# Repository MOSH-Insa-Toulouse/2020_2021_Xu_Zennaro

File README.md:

# 2020_2021_Xu_Zennaro

MOSH-KiCAD Project

# TASKS

- [x] MOSH
- [x] KiCAD

---

### KiCad - Shield for Arduino

- [x] Créer un projet de PCB pour réaliser une shield Arduino
- [x] Saisi du schéma
- [x] Vérification des tests électriques **ERC**
- [x] Association des empreintes de composants avec leur boitier
- [ ] Combiner les modèles 3D aux empreintes
- [x] Génération de la netlist
- [x] Placement des composants
- [x] Router les pistes de la carte électronique

#### KiCad Tools used

[KiCad EDA - Schematic Capture & PCB Design Software](https://kicad-pcb.org/), version: 5.1.8

Open source EDA / electronics CAD software for Windows, macOS and Linux.

#### Librairies de composants

* LTC1050:
* Resistor_THT:R_Axial_DIN0207_L6.3mm_D2.5mm_P10.16mm_Horizontal
* Capacitor
* Arduino Uno
* Conn_01x03:Pin
* RN2483

## Electrical diagram

## Component placement

## Routage

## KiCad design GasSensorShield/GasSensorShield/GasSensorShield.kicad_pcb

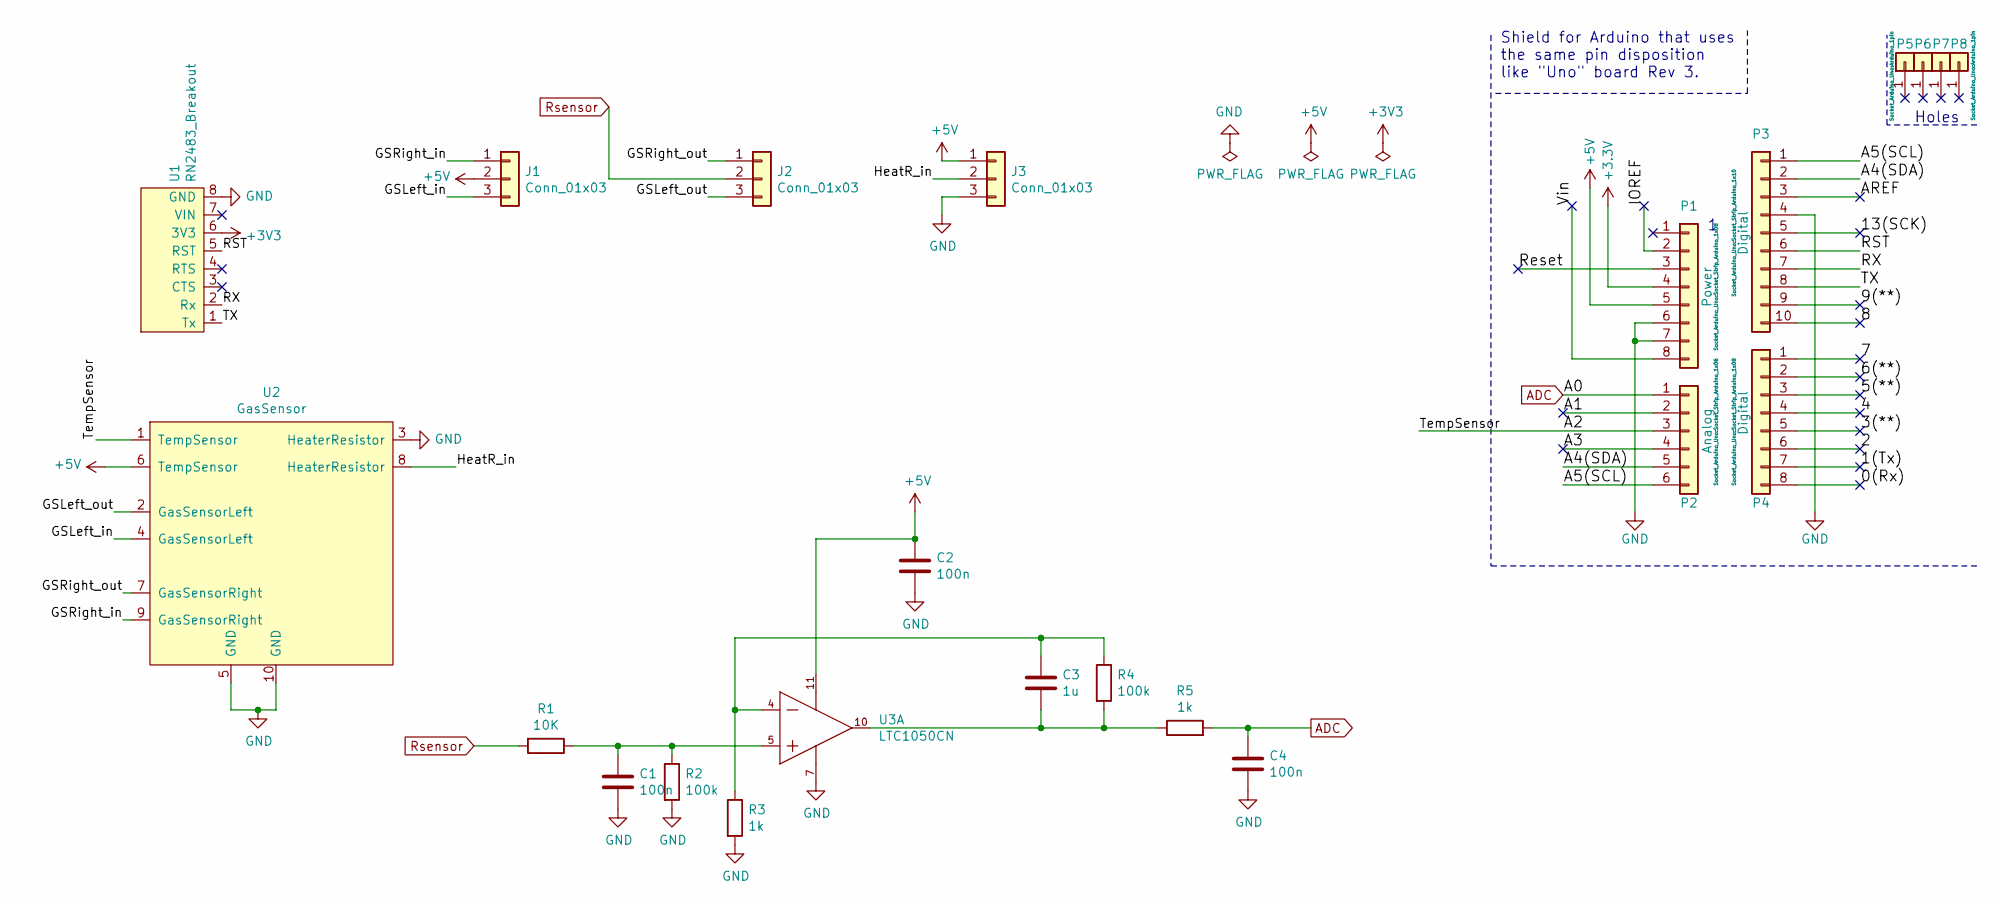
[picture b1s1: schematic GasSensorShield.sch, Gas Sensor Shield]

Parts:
C1, C2, C4: 100n; C_Disc_D4.3mm_W1.9mm_P5.00mm
C3: 1u; C_Disc_D4.3mm_W1.9mm_P5.00mm
J1, J2, J3: Conn_01x03; PinHeader_1x03_P2.00mm_Vertical
P1: Power; Socket_Strip_Arduino_1x08
P2: Analog; Socket_Strip_Arduino_1x06
P3: Digital; Socket_Strip_Arduino_1x10
P4: Digital; Socket_Strip_Arduino_1x08
P5, P6, P7, P8: CONN_01X01; Arduino_1pin
R1: 10K; R_Axial_DIN0207_L6.3mm_D2.5mm_P10.16mm_Horizontal
R2, R4: 100k; R_Axial_DIN0207_L6.3mm_D2.5mm_P10.16mm_Horizontal
R3, R5: 1k; R_Axial_DIN0207_L6.3mm_D2.5mm_P10.16mm_Horizontal
U1: RN2483_Breakout; Module_RN2483_Breakout
U2: GasSensor; TO-5-10
U3: LTC1050CN; Linear_Technology-LTC1050CN-Manufacturer_Recommended

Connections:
+5V: C2.1, J1.2, J3.1, P1.5, U2.6 (TempSensor), U3.11 (V+)
/0(Rx): P4.8
/1(Tx): P4.7
/2: P4.6
/3(**): P4.5
/4: P4.4
/5(**): P4.3
/6(**): P4.2
/7: P4.1
/8: P3.10
/9(**): P3.9
/13(SCK): P3.5
/A1: P2.2
/A2: P2.3, U2.1 (TempSensor)
/A3: P2.4
/A4(SDA): P2.5, P3.2
/A5(SCL): P2.6, P3.1
/AREF: P3.3
/GSLeft_in: J1.3, U2.4 (GasSensorLeft)
/GSLeft_out: J2.3, U2.2 (GasSensorLeft)
/GSRight_in: J1.1, U2.9 (GasSensorRight)
/GSRight_out: J2.1, U2.7 (GasSensorRight)
/HeatR_in: J3.2, U2.8 (HeaterResistor)
/IOREF: P1.2
/RST: P3.6, U1.5 (RST)
/RX: P3.7, U1.2 (Rx)
/Reset: P1.3
/TX: P3.8, U1.1 (Tx)
/Vin: P1.8
ADC: C4.1, P2.1, R5.2
GND: C1.2, C2.2, C4.2, J3.3, P1.6, P1.7, P3.4, R2.2, R3.2, U1.8 (GND), U2.3 (HeaterResistor), U2.5 (GND), U2.10 (GND), U3.7 (V-)
unnamed: C1.1, R1.1, R2.1, U3.5 (+IN)
unnamed: C3.1, R3.1, R4.1, U3.4 (-IN)
unnamed: C3.2, R4.2, R5.1, U3.10 (OUT)
Rsensor: J2.2, R1.2

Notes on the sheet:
Holes
Shield for Arduino that uses the same pin disposition like "Uno" board Rev 3.

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
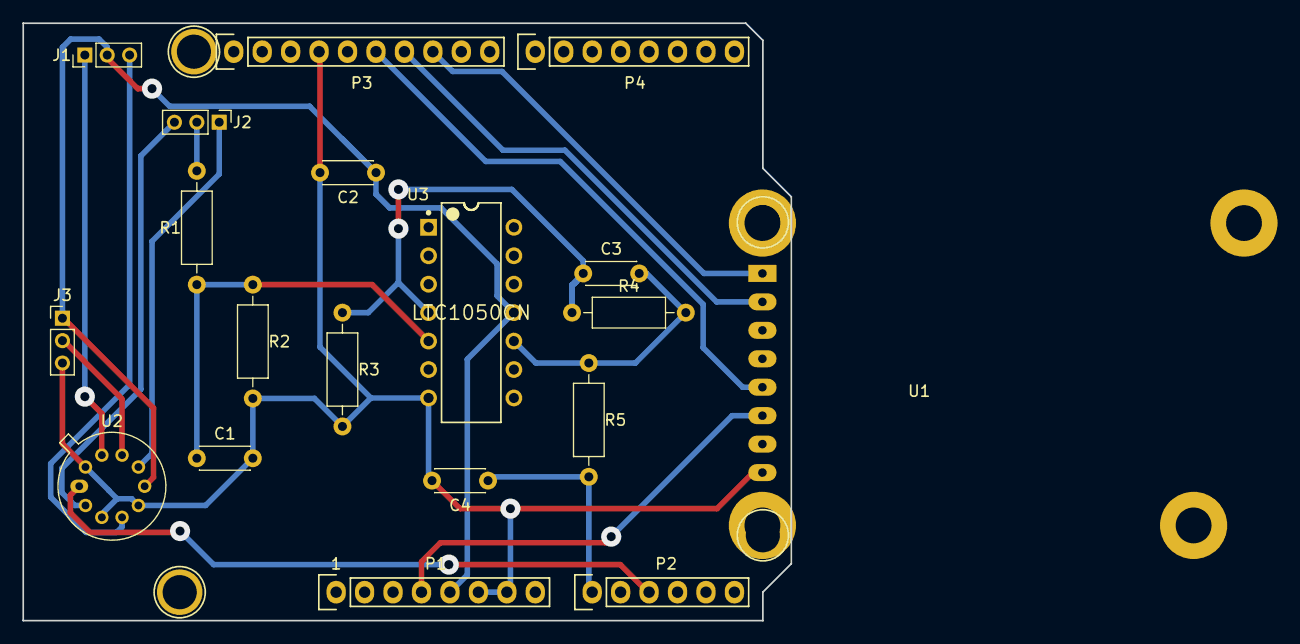
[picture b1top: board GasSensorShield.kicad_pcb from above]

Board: 2 copper layers, 68.6 x 53.3 mm, 23 parts (0 on the bottom side), 19 nets.

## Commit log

2020-12-07 ajout code Arduino
2020-12-07 ltspice
2020-12-08 ajout schemas LTSpice
2020-12-13 code arduino
2020-12-26 schematic KiCAD du shield + module loRa
2020-12-28 debut empreinte RN2483
2020-12-28 empreinte rn2483
2021-01-03 Added libs to project path
2021-01-03 Finishing KiCAD & TODO: README.md
2021-01-03 Fixed typo
